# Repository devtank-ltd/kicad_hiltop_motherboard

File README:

Copyright Devtank Ltd 2021.

This documentation describes Open Hardware and is Licensed under CERN-OHL-W v2.

You may redistribute and modify this documentation under the terms of the CERN-OHL-W v2 (https://cern.ch/cern-ohl). This documentation is distributed WITHOUT ANY EXPRESS OR IMPLIED WARRANTY, INCLUDING OF MERCHANTABILITY, SATISFACTORY QUALITY AND FITNESS FOR A PARTICULAR PURPOSE. Please see the CERN-OHL-W v2 for applicable conditions

Source location: git@github.com:devtank-ltd/hiltop_motherboard.git 

As per CERN-OHL-W v2 section 4.1, should You produce hardware based on these sources, You must maintain the   Source Location visible on the external case of the HILTOP or other product you make using this documentation.

This folder contains HILTOP Motherboard hardware schematics, PCB layout and BOM files. 

You will need Kicad to open hardware design files.

HILTOP Motherboards and other test and measurement products can be purchased directly from Devtank Ltd.

Please contact:
Tim Telford
CTO - Devtank Ltd
+44 (0)1332 650944

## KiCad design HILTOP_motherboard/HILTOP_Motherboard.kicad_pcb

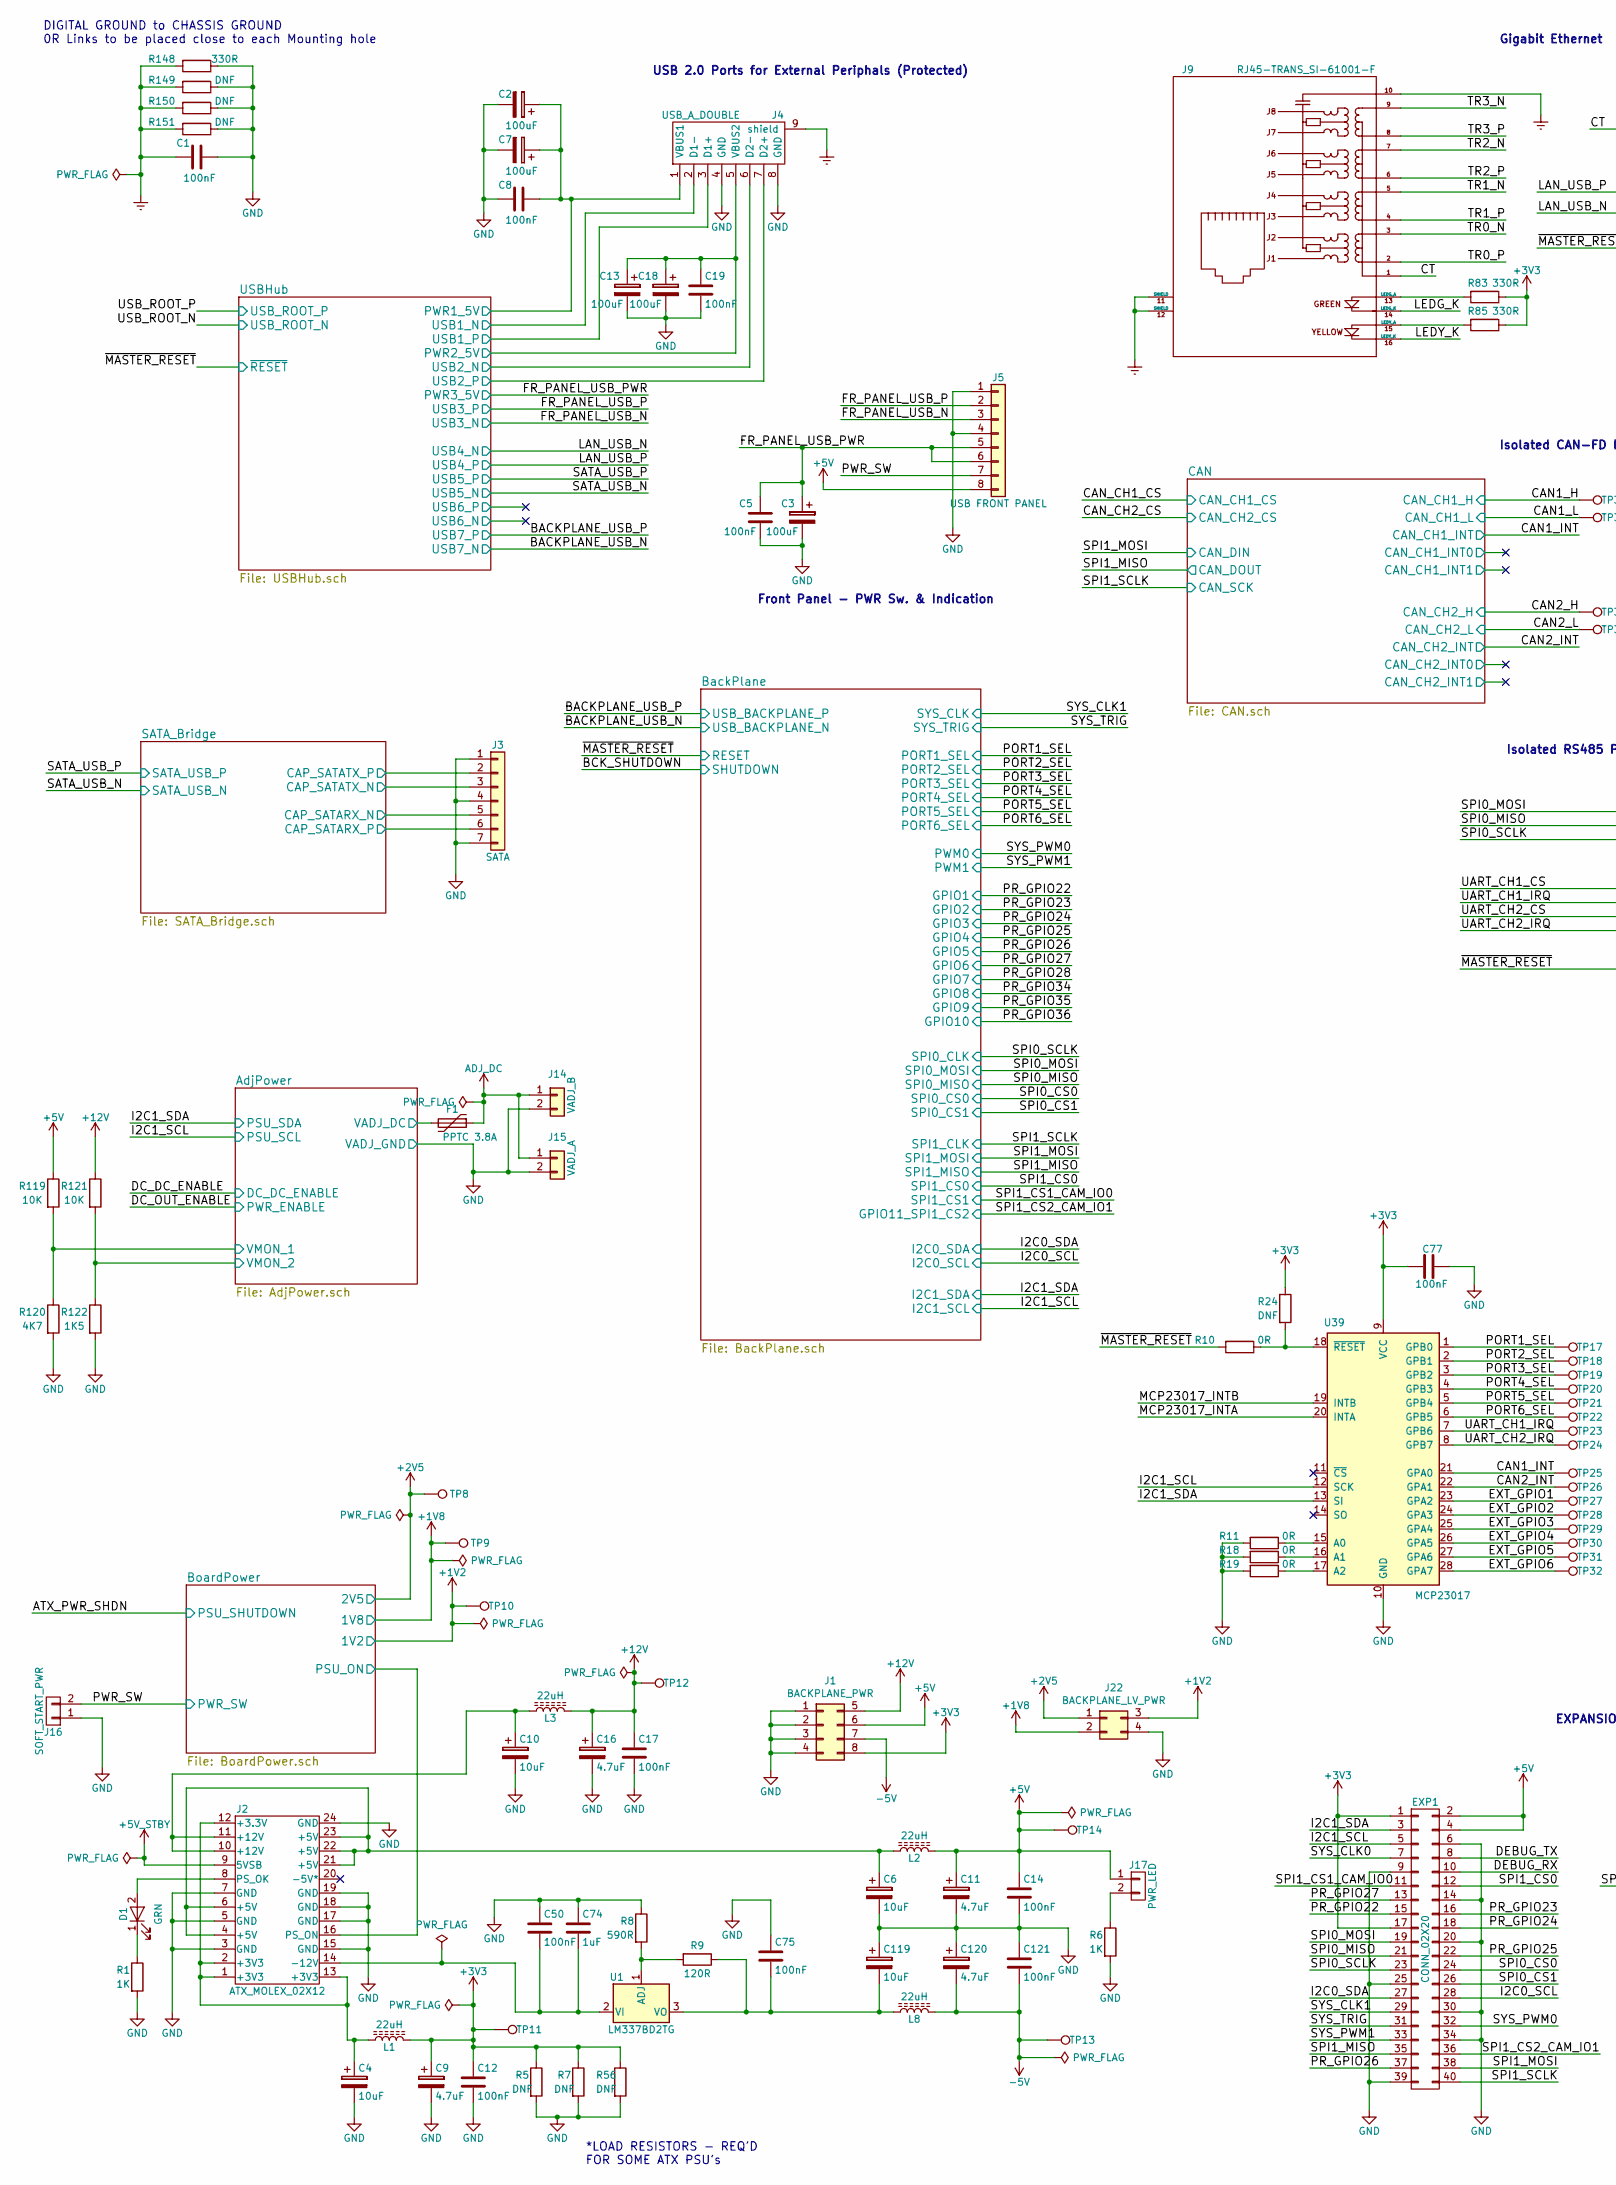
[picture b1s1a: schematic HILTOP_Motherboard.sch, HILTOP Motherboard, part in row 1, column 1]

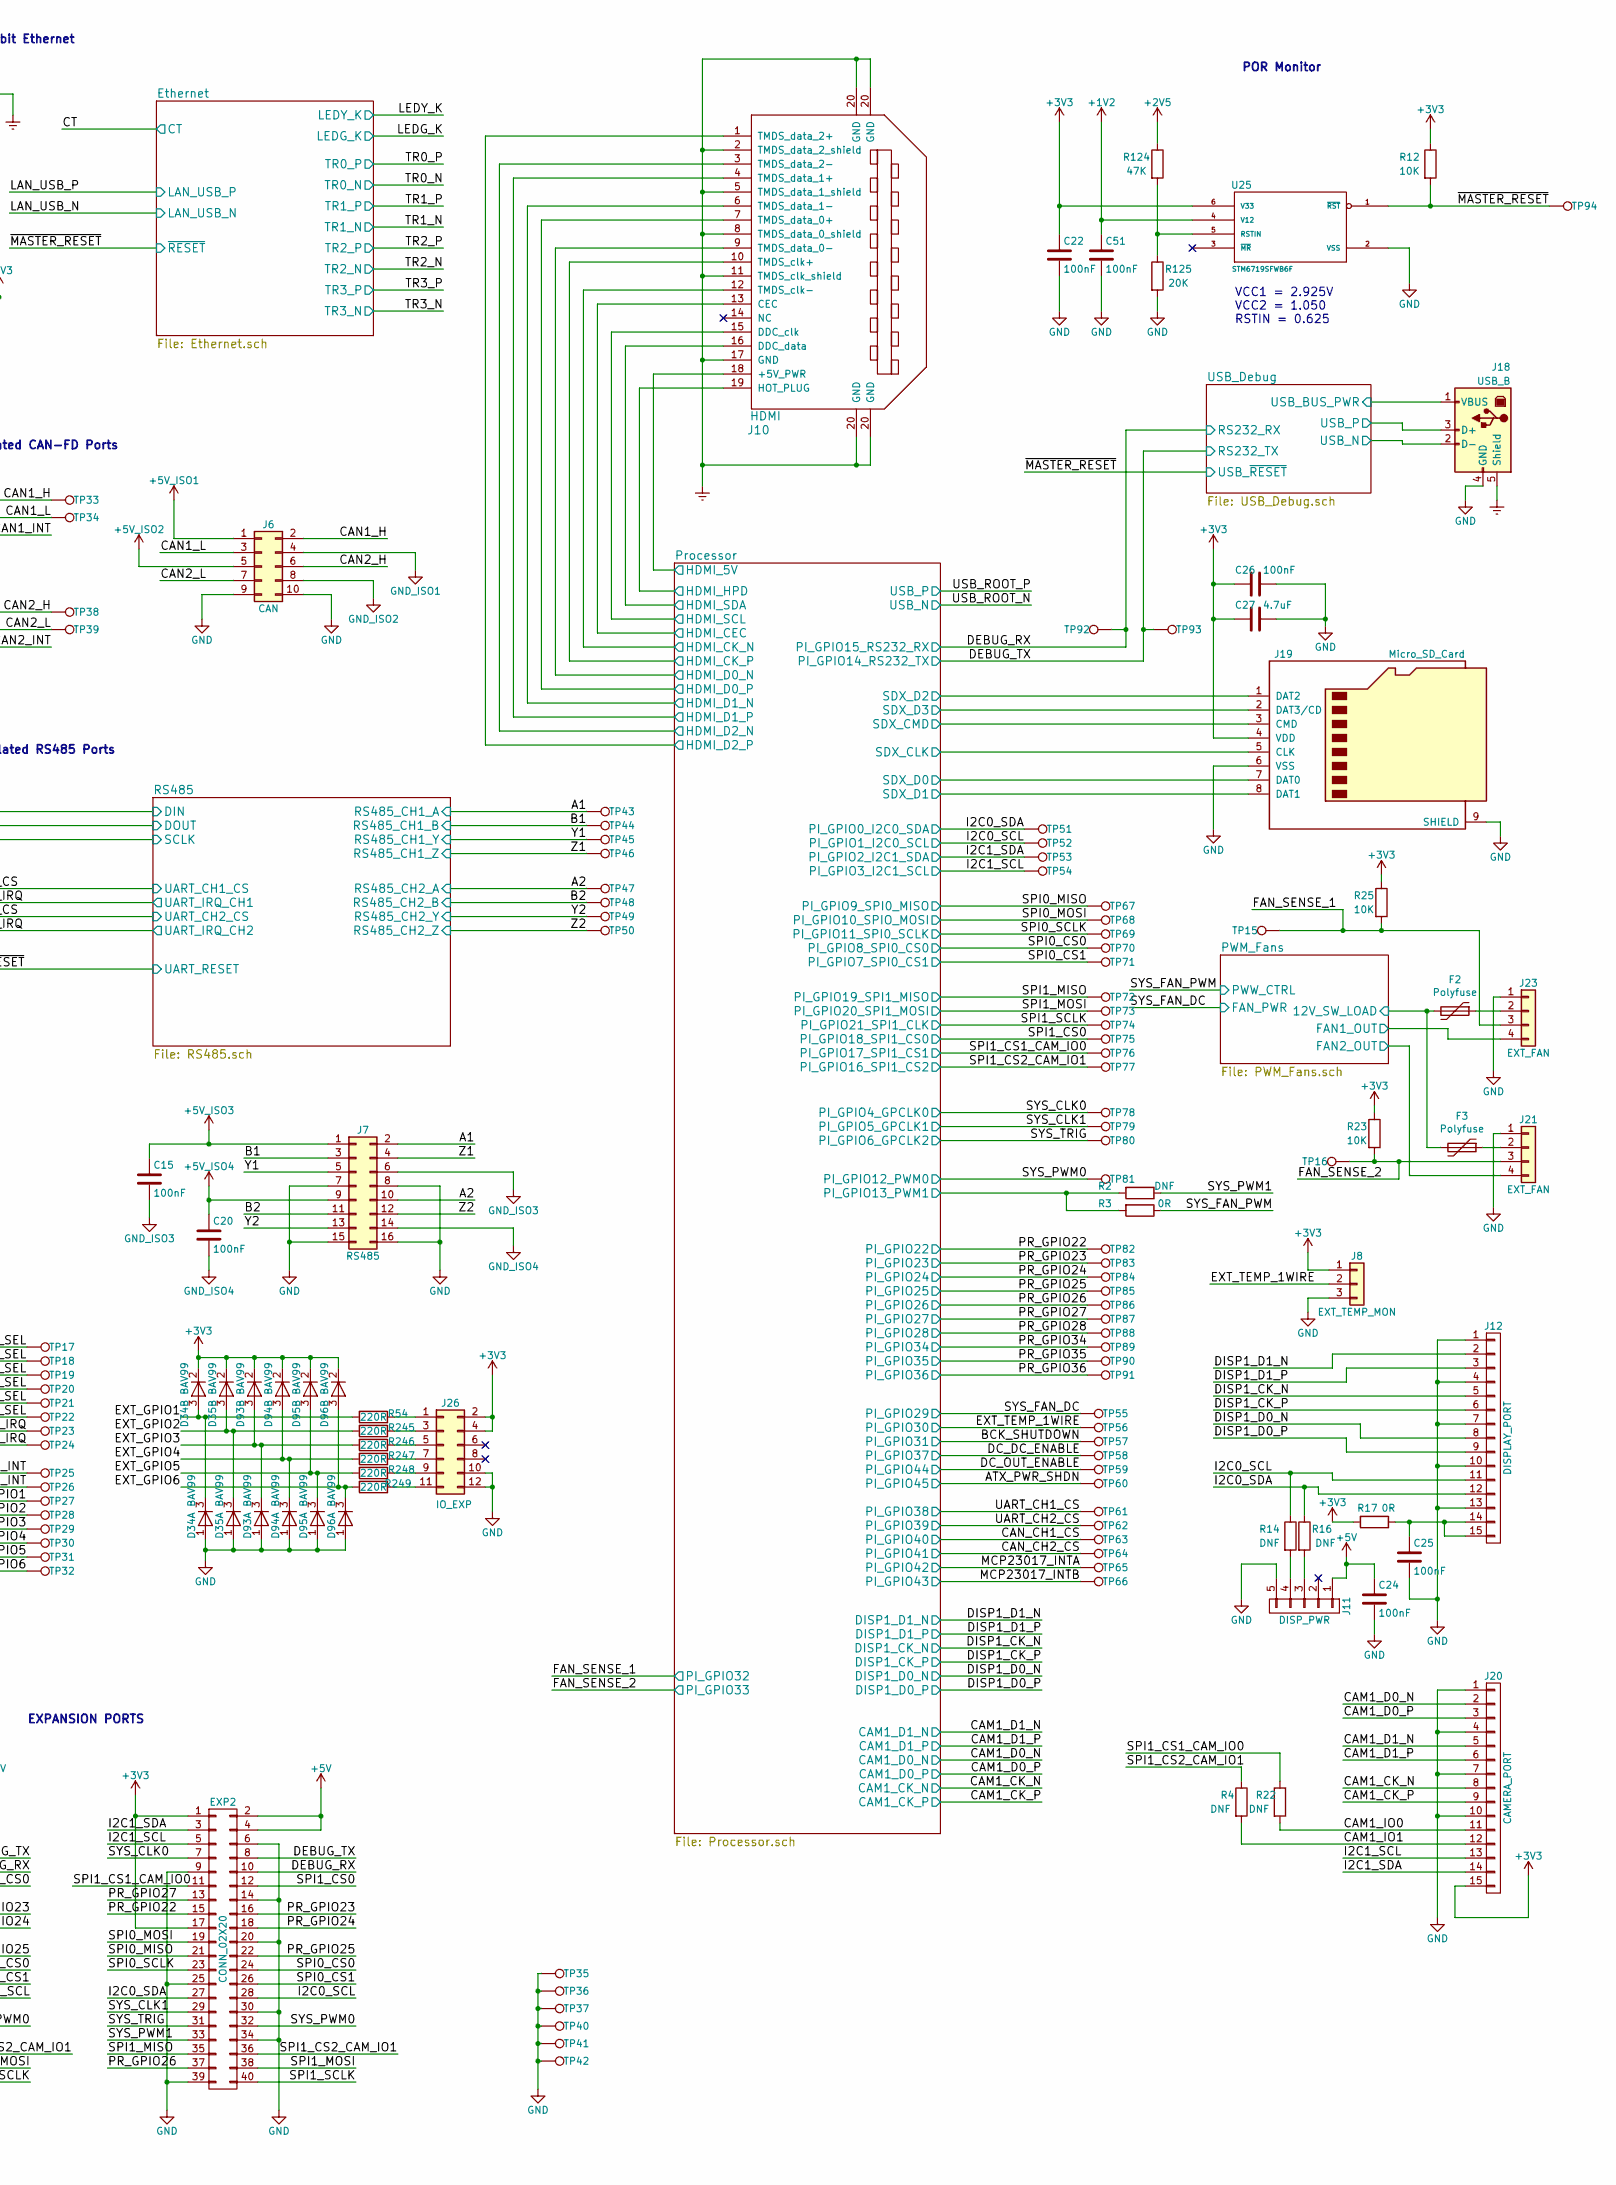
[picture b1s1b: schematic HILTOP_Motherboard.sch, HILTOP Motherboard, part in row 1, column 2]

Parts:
C1: 100nF; C_1210_3225Metric
C2, C3, C7, C13, C18: 100uF; CP_Elec_6.3x7.7
C4, C6, C10, C119: 10uF; CP_Elec_6.3x5.3
C5, C8, C12, C14, C15, C17, C19, C20, C22, C24, C25, C26, C50, C75, C77, C121: 100nF; C_0603_1608Metric
C9, C11, C16, C120: 4.7uF; CP_Elec_5x5.3
C27: 4.7uF; C_0805_2012Metric
C51: 100nF; C_0402_1005Metric
C74: 1uF; C_0805_2012Metric
D1: GRN; LED_0402_1005Metric
D34, D35, D93, D94, D95, D96: BAV99; SOT-23
EXP1, EXP2: CONN_02X20; IDC-Header_2x20_P2.54mm_Vertical
F1: PPTC 3.8A; Fuse_Bourns_MF-RHT200
F2, F3: Polyfuse; Fuse_1206_3216Metric
J1: BACKPLANE_PWR; Molex_Mini-Fit_Jr_5566-08A_2x04_P4.20mm_Vertical
J2: ATX_MOLEX_02X12; Molex_MiniFit-JR-5556-24A_2x12x4.20mm_Straight
J3: SATA; SATA-7_THT_VERT_1
J4: USB_A_DOUBLE; USB_A_Double_Lumberg_2410_03
J5: USB FRONT PANEL; Molex_Picoflex_90325-0008_2x04_P1.27mm_Vertical
J6: CAN; Molex_Picoflex_90325-0010_2x05_P1.27mm_Vertical
J7: RS485; Molex_Picoflex_90325-0016_2x08_P1.27mm_Vertical
J8: EXT_TEMP_MON; Molex_KK-254_AE-6410-03A_1x03_P2.54mm_Vertical
J9: RJ45-TRANS_SI-61001-F; RJ45_TRANSFO_STEWART
J10: HDMI; FCI_10029449-11RLF
J11: DISP_PWR; Molex_KK-254_AE-6410-05A_1x05_P2.54mm_Vertical
J12: DISPLAY_PORT; DSI_FCC15W_VERT
J14: VADJ_B; Molex_MiniFit-JR-5556-02A_2x01x4.20mm_Straight
J15: VADJ_A; Molex_MiniFit-JR-5556-02A_2x01x4.20mm_Straight
J16: SOFT_START_PWR; Pin_Header_Straight_1x02_Pitch2.54mm
J17: PWR_LED; Pin_Header_Straight_1x02_Pitch2.54mm
J18: USB_B; USB_B_Horizontal
J19: Micro_SD_Card; uSD_MSDC-PP03
J20: CAMERA_PORT; DSI_FCC15W_VERT
J21, J23: EXT_FAN; Molex_KK-254_AE-6410-04A_1x04_P2.54mm_Vertical
J22: BACKPLANE_LV_PWR; Molex_Mini-Fit_Jr_5566-04A_2x02_P4.20mm_Vertical
J26: IO_EXP; IDC-Header_2x06_P2.54mm_Vertical
L1, L2, L3, L8: 22uH; Inductor_8x8
R1, R6: 1K; R_0603_1608Metric
R2, R4, R14, R16, R22, R24: DNF; R_0603_1608Metric
R3, R10, R11, R17, R18, R19: 0R; R_0603_1608Metric
R5, R7, R56: DNF; R_1206_3216Metric
R8: 590R; R_1206_3216Metric
R9: 120R; R_0603_1608Metric
R12, R23, R25, R119, R121: 10K; R_0603_1608Metric
R54, R245, R246, R247, R248, R249: 220R; R_0402_1005Metric
R83, R85: 330R; R_0603_1608Metric
R120: 4K7; R_0603_1608Metric
R122: 1K5; R_0603_1608Metric
R124: 47K; R_0603_1608Metric
R125: 20K; R_0603_1608Metric
R148: 330R; R_1210_3225Metric
R149, R150, R151: DNF; R_1210_3225Metric
TP8, TP9, TP10, TP11, TP12, TP13, TP14, TP15, TP16, TP17, TP18, TP19, TP20, TP21, TP22, TP23, TP24, TP25, TP26, TP27, TP28, TP29, TP30, TP31, TP32, TP33, TP34, TP35, TP36, TP37, TP38, TP39, TP40, TP41, TP42, TP43, TP44, TP45, TP46, TP47, TP48, TP49, TP50, TP51, TP52, TP53, TP54, TP55, TP56, TP57, TP58, TP59, TP60, TP61, TP62, TP63, TP64, TP65, TP66, TP67, TP68, TP69, TP70, TP71, TP72, TP73, TP74, TP75, TP76, TP77, TP78, TP79, TP80, TP81, TP82, TP83, TP84, TP85, TP86, TP87, TP88, TP89, TP90, TP91, TP92, TP93, TP94: TP; TestPoint_THTPad_D1.0mm_Drill0.5mm
U1: LM337BD2TG; TO-263-2
U25: STM6719SFWB6F; TSOT-23-6
U39: MCP23017; SSOP-28_5.3x10.2mm_P0.65mm

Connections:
+1V2: C51.1, J22.3, TP10.1, U25.4 (V12); also elsewhere on the board
+1V8: J22.2, TP9.1; also elsewhere on the board
+2V5: J22.1, R124.1, TP8.1; also elsewhere on the board
+2V5_LAN_A: J9.1; also elsewhere on the board
+3V3: C9.1, C12.1, C22.1, C26.2, C27.2, C77.2, D34.2 (K), D35.2 (K), D93.2 (K), D94.2 (K), D95.2 (K), D96.2 (K), EXP1.1, EXP1.17, EXP2.1, EXP2.17, J1.8, J8.1, J19.4 (VDD), J20.15, J26.2, J26.4, L1.2, R5.1, R7.1, R12.1, R17.2, R23.1, R24.1, R25.1, R56.1, R83.1, R85.1, TP11.1, U25.6 (V33), U39.9 (VCC); also elsewhere on the board
+5V_ISO1: J6.1; also elsewhere on the board
+5V_ISO2: J6.5; also elsewhere on the board
+5V_STBY: J2.9 (5VSB); also elsewhere on the board
+12V: C16.1, C17.1, J1.5, L3.2, R121.1, TP12.1; also elsewhere on the board
-5V: C120.2, C121.2, J1.7, L8.2, TP13.1; also elsewhere on the board
/A1: J7.2, TP43.1; also elsewhere on the board
/A2: J7.10, TP47.1; also elsewhere on the board
/ATX_PWR_SHDN: TP60.1; also elsewhere on the board
/AdjPower/VADJ_DC: F1.2; also elsewhere on the board
/AdjPower/VMON_1: R119.2, R120.1; also elsewhere on the board
/AdjPower/VMON_2: R121.2, R122.1; also elsewhere on the board
/B1: J7.3, TP44.1; also elsewhere on the board
/B2: J7.11, TP48.1; also elsewhere on the board
/BCK_SHUTDOWN: TP57.1; also elsewhere on the board
/BoardPower/PSU_ON: J2.16 (PS_ON); also elsewhere on the board
/CAM1_CK_N: J20.8; also elsewhere on the board
/CAM1_CK_P: J20.9; also elsewhere on the board
/CAM1_D0_N: J20.2; also elsewhere on the board
/CAM1_D0_P: J20.3; also elsewhere on the board
/CAM1_D1_N: J20.5; also elsewhere on the board
/CAM1_D1_P: J20.6; also elsewhere on the board
/CAM1_IO0: J20.11, R22.2
/CAM1_IO1: J20.12, R4.2
/CAN1_H: J6.2, TP33.1; also elsewhere on the board
/CAN1_INT: TP25.1, U39.21 (GPA0); also elsewhere on the board
/CAN1_L: J6.3, TP34.1; also elsewhere on the board
/CAN2_H: J6.6, TP38.1; also elsewhere on the board
/CAN2_INT: TP26.1, U39.22 (GPA1); also elsewhere on the board
/CAN2_L: J6.7, TP39.1; also elsewhere on the board
/CAN_CH1_CS: TP63.1; also elsewhere on the board
/CAN_CH2_CS: TP64.1; also elsewhere on the board
/DC_DC_ENABLE: TP58.1; also elsewhere on the board
/DC_OUT_ENABLE: TP59.1; also elsewhere on the board
/DEBUG_RX: EXP1.10, EXP2.10, TP92.1; also elsewhere on the board
/DEBUG_TX: EXP1.8, EXP2.8, TP93.1; also elsewhere on the board
/DISP1_CK_N: J12.5; also elsewhere on the board
/DISP1_CK_P: J12.6; also elsewhere on the board
/DISP1_D0_N: J12.8; also elsewhere on the board
/DISP1_D0_P: J12.9; also elsewhere on the board
/DISP1_D1_N: J12.2; also elsewhere on the board
/DISP1_D1_P: J12.3; also elsewhere on the board
/EXT_GPIO1: D34.3 (K), R54.2, TP27.1, U39.23 (GPA2)
/EXT_GPIO2: D35.3 (K), R245.2, TP28.1, U39.24 (GPA3)
/EXT_GPIO3: D93.3 (K), R246.2, TP29.1, U39.25 (GPA4)
/EXT_GPIO4: D94.3 (K), R247.2, TP30.1, U39.26 (GPA5)
/EXT_GPIO5: D95.3 (K), R248.2, TP31.1, U39.27 (GPA6)
/EXT_GPIO6: D96.3 (K), R249.2, TP32.1, U39.28 (GPA7)
/EXT_TEMP_1WIRE: J8.2, TP56.1; also elsewhere on the board
/FAN_SENSE_1: J23.3, R25.2, TP15.1; also elsewhere on the board
/FAN_SENSE_2: J21.3, R23.2, TP16.1; also elsewhere on the board
/FR_PANEL_USB_N: J5.3; also elsewhere on the board
/FR_PANEL_USB_P: J5.2; also elsewhere on the board
/FR_PANEL_USB_PWR: C3.1, C5.1, J5.5, J5.6; also elsewhere on the board
/I2C0_SCL: EXP1.28, EXP2.28, J12.11, R14.1, TP52.1; also elsewhere on the board
/I2C0_SDA: EXP1.27, EXP2.27, J12.12, R16.1, TP51.1; also elsewhere on the board
/I2C1_SCL: EXP1.5, EXP2.5, J20.13, TP54.1, U39.12 (SCK); also elsewhere on the board
/I2C1_SDA: EXP1.3, EXP2.3, J20.14, TP53.1, U39.13 (SI); also elsewhere on the board
/LEDG_K: J9.14 (LEDG_K); also elsewhere on the board
/LEDY_K: J9.16 (LEDY_K); also elsewhere on the board
/MCP23017_INTA: TP65.1, U39.20 (INTA); also elsewhere on the board
/MCP23017_INTB: TP66.1, U39.19 (INTB); also elsewhere on the board
/PORT1_SEL: TP17.1, U39.1 (GPB0); also elsewhere on the board
/PORT2_SEL: TP18.1, U39.2 (GPB1); also elsewhere on the board
/PORT3_SEL: TP19.1, U39.3 (GPB2); also elsewhere on the board
/PORT4_SEL: TP20.1, U39.4 (GPB3); also elsewhere on the board
/PORT5_SEL: TP21.1, U39.5 (GPB4); also elsewhere on the board
/PORT6_SEL: TP22.1, U39.6 (GPB5); also elsewhere on the board
/PR_GPIO22: EXP1.15, EXP2.15, TP82.1; also elsewhere on the board
/PR_GPIO23: EXP1.16, EXP2.16, TP83.1; also elsewhere on the board
/PR_GPIO24: EXP1.18, EXP2.18, TP84.1; also elsewhere on the board
/PR_GPIO25: EXP1.22, EXP2.22, TP85.1; also elsewhere on the board
/PR_GPIO26: EXP1.37, EXP2.37, TP86.1; also elsewhere on the board
/PR_GPIO27: EXP1.13, EXP2.13, TP87.1; also elsewhere on the board
/PR_GPIO28: TP88.1; also elsewhere on the board
/PR_GPIO34: TP89.1; also elsewhere on the board
/PR_GPIO35: TP90.1; also elsewhere on the board
/PR_GPIO36: TP91.1; also elsewhere on the board
/PWM_Fans/12V_SW_LOAD: F2.2, F3.2; also elsewhere on the board
/PWM_Fans/FAN1_OUT: J23.4; also elsewhere on the board
/PWM_Fans/FAN2_OUT: J21.4; also elsewhere on the board
/PWR_SW: J5.7, J16.2; also elsewhere on the board
/Processor/HDMI_5V: J10.18 (+5V_PWR); also elsewhere on the board
/Processor/HDMI_CEC: J10.13 (CEC); also elsewhere on the board
/Processor/HDMI_CK_N: J10.12 (TMDS_clk-); also elsewhere on the board
/Processor/HDMI_CK_P: J10.10 (TMDS_clk+); also elsewhere on the board
/Processor/HDMI_D0_N: J10.9 (TMDS_data_0-); also elsewhere on the board
/Processor/HDMI_D0_P: J10.7 (TMDS_data_0+); also elsewhere on the board
/Processor/HDMI_D1_N: J10.6 (TMDS_data_1-); also elsewhere on the board
/Processor/HDMI_D1_P: J10.4 (TMDS_data_1+); also elsewhere on the board
/Processor/HDMI_D2_N: J10.3 (TMDS_data_2-); also elsewhere on the board
/Processor/HDMI_D2_P: J10.1 (TMDS_data_2+); also elsewhere on the board
/Processor/HDMI_HPD: J10.19 (HOT_PLUG); also elsewhere on the board
/Processor/HDMI_SCL: J10.15 (DDC_clk); also elsewhere on the board
/Processor/HDMI_SDA: J10.16 (DDC_data); also elsewhere on the board
/Processor/PI_GPIO13_PWM1: R2.2, R3.2; also elsewhere on the board
/Processor/SDX_CLK: J19.5 (CLK); also elsewhere on the board
/Processor/SDX_CMD: J19.3 (CMD); also elsewhere on the board
/Processor/SDX_D0: J19.7 (DAT0); also elsewhere on the board
/Processor/SDX_D1: J19.8 (DAT1); also elsewhere on the board
/Processor/SDX_D2: J19.1 (DAT2); also elsewhere on the board
/Processor/SDX_D3: J19.2 (DAT3/CD); also elsewhere on the board
/SATA_Bridge/CAP_SATARX_N: J3.5; also elsewhere on the board
/SATA_Bridge/CAP_SATARX_P: J3.6; also elsewhere on the board
/SATA_Bridge/CAP_SATATX_N: J3.3; also elsewhere on the board
/SATA_Bridge/CAP_SATATX_P: J3.2; also elsewhere on the board
/SPI0_CS0: EXP1.24, EXP2.24, TP70.1; also elsewhere on the board
/SPI0_CS1: EXP1.26, EXP2.26, TP71.1; also elsewhere on the board
/SPI0_MISO: EXP1.21, EXP2.21, TP67.1; also elsewhere on the board
/SPI0_MOSI: EXP1.19, EXP2.19, TP68.1; also elsewhere on the board
/SPI0_SCLK: EXP1.23, EXP2.23, TP69.1; also elsewhere on the board
/SPI1_CS0: EXP1.12, EXP2.12, TP75.1; also elsewhere on the board
/SPI1_CS1_CAM_IO0: EXP1.11, EXP2.11, R22.1, TP76.1; also elsewhere on the board
/SPI1_CS2_CAM_IO1: EXP1.36, EXP2.36, R4.1, TP77.1; also elsewhere on the board
/SPI1_MISO: EXP1.35, EXP2.35, TP72.1; also elsewhere on the board
/SPI1_MOSI: EXP1.38, EXP2.38, TP73.1; also elsewhere on the board
/SPI1_SCLK: EXP1.40, EXP2.40, TP74.1; also elsewhere on the board
/SYS_CLK0: EXP1.7, EXP2.7, TP78.1; also elsewhere on the board
/SYS_CLK1: EXP1.29, EXP2.29, TP79.1; also elsewhere on the board
/SYS_FAN_DC: TP55.1; also elsewhere on the board
/SYS_FAN_PWM: R3.1; also elsewhere on the board
/SYS_PWM0: EXP1.32, EXP2.32, TP81.1; also elsewhere on the board
/SYS_PWM1: EXP1.33, EXP2.33, R2.1; also elsewhere on the board
/SYS_TRIG: EXP1.31, EXP2.31, TP80.1; also elsewhere on the board
/TR0_N: J9.3; also elsewhere on the board
/TR0_P: J9.2; also elsewhere on the board
/TR1_N: J9.5; also elsewhere on the board
/TR1_P: J9.4; also elsewhere on the board
/TR2_N: J9.7; also elsewhere on the board
/TR2_P: J9.6; also elsewhere on the board
/TR3_N: J9.9; also elsewhere on the board
/TR3_P: J9.8; also elsewhere on the board
/UART_CH1_CS: TP61.1; also elsewhere on the board
/UART_CH1_IRQ: TP23.1, U39.7 (GPB6); also elsewhere on the board
/UART_CH2_CS: TP62.1; also elsewhere on the board
/UART_CH2_IRQ: TP24.1, U39.8 (GPB7); also elsewhere on the board
/USBHub/PWR1_5V: C2.1, C7.1, C8.1, J4.1 (VBUS1); also elsewhere on the board
/USBHub/PWR2_5V: C13.1, C18.1, C19.1, J4.5 (VBUS2); also elsewhere on the board
/USBHub/USB1_N: J4.2 (D1-); also elsewhere on the board
/USBHub/USB1_P: J4.3 (D1+); also elsewhere on the board
/USBHub/USB2_N: J4.6 (D2-); also elsewhere on the board
/USBHub/USB2_P: J4.7 (D2+); also elsewhere on the board
/USB_Debug/USB_BUS_PWR: J18.1 (VBUS); also elsewhere on the board
/USB_Debug/USB_N: J18.2 (D-); also elsewhere on the board
/USB_Debug/USB_P: J18.3 (D+); also elsewhere on the board
/Y1: J7.5, TP45.1; also elsewhere on the board
/Y2: J7.13, TP49.1; also elsewhere on the board
/Z1: J7.4, TP46.1; also elsewhere on the board
/Z2: J7.12, TP50.1; also elsewhere on the board
/~MASTER_RESET: R10.2, R12.2, TP94.1, U25.1 (~RST); also elsewhere on the board
ADJ_DC: F1.1, J14.1, J15.1
Earth: C1.2, J4.9 (shield), J9.10, J9.11 (SHIELD), J9.12 (SHIELD), J10.2 (TMDS_data_2_shield), J10.5 (TMDS_data_1_shield), J10.8 (TMDS_data_0_shield), J10.11 (TMDS_clk_shield), J10.17 (GND), J10.20 (GND), J18.5 (Shield), R148.2, R149.2, R150.2, R151.2
GND: C1.1, C2.2, C3.2, C4.2, C5.2, C6.2, C7.2, C8.2, C9.2, C10.2, C11.2, C12.2, C13.2, C14.2, C16.2, C17.2, C18.2, C19.2, C22.2, C24.2, C25.2, C26.1, C27.1, C50.1, C51.2, C74.1, C75.1, C77.1, C119.1, C120.1, C121.1, D34.1 (A), D35.1 (A), D93.1 (A), D94.1 (A), D95.1 (A), D96.1 (A), EXP1.6, EXP1.9, EXP1.14, EXP1.20, EXP1.25, EXP1.30, EXP1.34, EXP1.39, EXP2.6, EXP2.9, EXP2.14, EXP2.20, EXP2.25, EXP2.30, EXP2.34, EXP2.39, J1.1, J1.2, J1.3, J1.4, J2.3 (GND), J2.5 (GND), J2.7 (GND), J2.15 (GND), J2.17 (GND), J2.18 (GND), J2.19 (GND), J2.24 (GND), J3.1, J3.4, J3.7, J4.4 (GND), J4.8 (GND), J5.1, J5.4, J6.9, J6.10, J7.7, J7.8, J7.15, J7.16, J8.3, J11.5, J12.1, J12.4, J12.7, J12.10, J12.13, J14.2, J15.2, J16.1, J18.4 (GND), J19.6 (VSS), J19.9 (SHIELD), J20.1, J20.4, J20.7, J20.10, J21.1, J22.4, J23.1, J26.10, J26.12, R1.2, R5.2, R6.2, R7.2, R8.1, R11.2, R18.2, R19.2, R56.2, R120.2, R122.2, R125.2, R148.1, R149.1, R150.1, R151.1, TP35.1, TP36.1, TP37.1, TP40.1, TP41.1, TP42.1, U25.2 (VSS), U39.10 (GND); also elsewhere on the board
GND_ISO1: J6.4; also elsewhere on the board
GND_ISO2: J6.8; also elsewhere on the board
GND_ISO3: C15.2, J7.6; also elsewhere on the board
GND_ISO4: C20.2, J7.14; also elsewhere on the board
unnamed: C4.1, J2.1 (+3V3), J2.2 (+3V3), J2.12 (+3.3V), J2.13 (+3V3), L1.1
unnamed: C6.1, J2.4 (+5V), J2.6 (+5V), J2.21 (+5V), J2.22 (+5V), J2.23 (+5V), L2.1
unnamed: C10.1, J2.10 (+12V), J2.11 (+12V), L3.1
unnamed: C25.1, J12.14, J12.15, R17.1
unnamed: C50.2, C74.2, J2.14 (-12V), U1.2 (VI)
unnamed: C75.2, C119.2, L8.1, R9.1, U1.3 (VO)
unnamed: D1.1 (K), R1.1
unnamed: D1.2 (A), J2.8 (PS_OK)
unnamed: F2.1, J23.2
unnamed: F3.1, J21.2
unnamed: J9.13 (LEDG_A), R83.2
unnamed: J9.15 (LEDY_A), R85.2
unnamed: J11.3, R16.2
unnamed: J11.4, R14.2
unnamed: J17.2, R6.1
unnamed: J26.1, R54.1
unnamed: J26.3, R245.1
unnamed: J26.5, R246.1
unnamed: J26.7, R247.1
unnamed: J26.9, R248.1
unnamed: J26.11, R249.1
unnamed: R8.2, R9.2, U1.1 (ADJ)
unnamed: R10.1, R24.2, U39.18 (~RESET)
unnamed: R11.1, U39.15 (A0)
unnamed: R18.1, U39.16 (A1)
unnamed: R19.1, U39.17 (A2)
unnamed: R124.2, R125.1, U25.5 (RSTIN)

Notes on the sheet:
*LOAD RESISTORS - REQ'D FOR SOME ATX PSU's
EXPANSION PORTS
VCC1 = 2.925V VCC2 = 1.050 RSTIN = 0.625
DIGITAL GROUND to CHASSIS GROUND 0R Links to be placed close to each Mounting hole
Isolated RS485 Ports
Isolated CAN-FD Ports
Gigabit Ethernet
USB 2.0 Ports for External Periphals (Protected)
POR Monitor
Front Panel - PWR Sw. & Indication

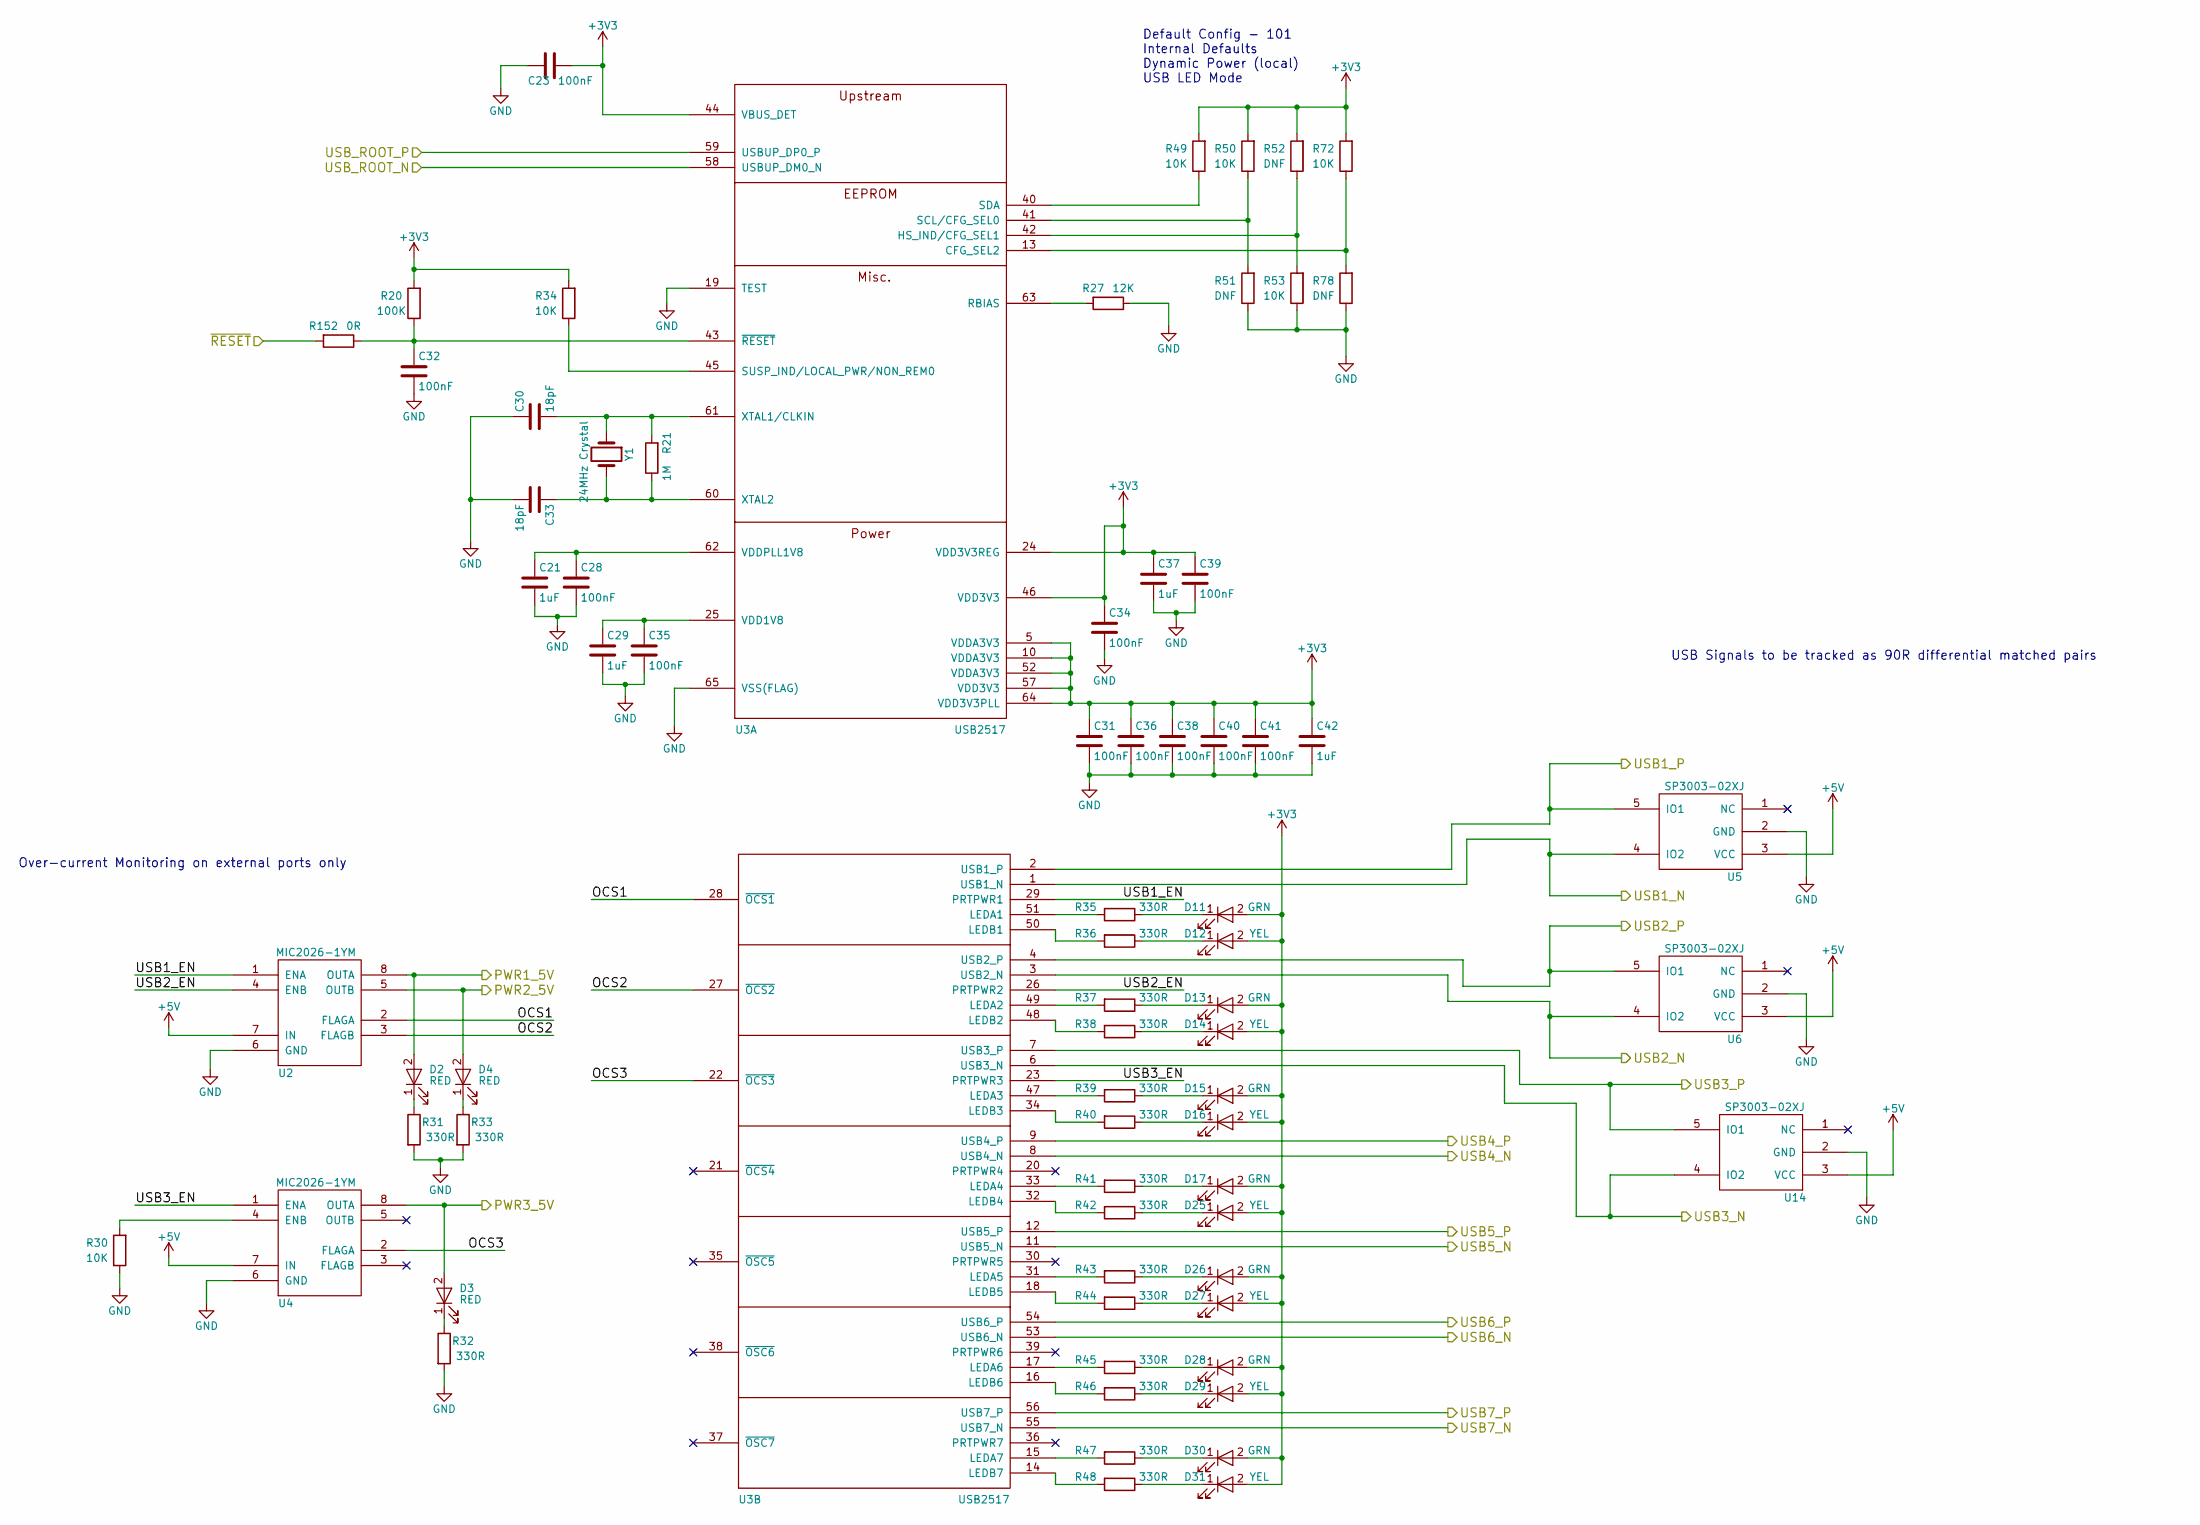
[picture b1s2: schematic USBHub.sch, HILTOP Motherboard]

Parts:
C21: 1uF; C_0603_1608Metric
C23: 100nF; C_0603_1608Metric
C28, C31, C32, C34, C35, C36, C38, C39, C40, C41: 100nF; C_0201_0603Metric
C29, C37, C42: 1uF; C_0201_0603Metric
C30, C33: 18pF; C_0201_0603Metric
D2, D3, D4: RED; LED_0402_1005Metric
D11, D13, D15, D17, D26, D28, D30: GRN; LED_0402_1005Metric
D12, D14, D16, D25, D27, D29, D31: YEL; LED_0402_1005Metric
R20: 100K; R_0603_1608Metric
R21: 1M; R_0603_1608Metric
R27: 12K; R_0603_1608Metric
R30, R34, R49, R50, R53, R72: 10K; R_0402_1005Metric
R31, R32, R33, R35, R36, R37, R38, R39, R40, R41, R42, R43, R44, R45, R46, R47, R48: 330R; R_0402_1005Metric
R51, R52, R78: DNF; R_0402_1005Metric
R152: 0R; R_0603_1608Metric
U2, U4: MIC2026-1YM; SOIC-8_3.9x4.9mm_P1.27mm
U3: USB2517; QFN-64-1EP_9x9mm_P0.5mm_EP4.7x4.7mm
U5, U6, U14: SP3003-02XJ; SC70-5
Y1: 24MHz Crystal; Crystal_SMD_7050-2Pin_7.0x5.0mm

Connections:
+3V3: C23.1, C31.1, C34.1, C36.1, C37.1, C38.1, C39.1, C40.1, C41.1, C42.1, D11.2 (A), D12.2 (A), D13.2 (A), D14.2 (A), D15.2 (A), D16.2 (A), D17.2 (A), D25.2 (A), D26.2 (A), D27.2 (A), D28.2 (A), D29.2 (A), D30.2 (A), D31.2 (A), R20.2, R34.2, R49.2, R50.2, R52.2, R72.2, U3.5 (VDDA3V3), U3.10 (VDDA3V3), U3.24 (VDD3V3REG), U3.44 (VBUS_DET), U3.46 (VDD3V3), U3.52 (VDDA3V3), U3.57 (VDD3V3), U3.64 (VDD3V3PLL); also elsewhere on the board
/BACKPLANE_USB_N: U3.55 (USB7_N); also elsewhere on the board
/BACKPLANE_USB_P: U3.56 (USB7_P); also elsewhere on the board
/FR_PANEL_USB_N: U3.6 (USB3_N), U14.4 (IO2); also elsewhere on the board
/FR_PANEL_USB_P: U3.7 (USB3_P), U14.5 (IO1); also elsewhere on the board
/FR_PANEL_USB_PWR: D3.2 (A), U4.8 (OUTA); also elsewhere on the board
/LAN_USB_N: U3.8 (USB4_N); also elsewhere on the board
/LAN_USB_P: U3.9 (USB4_P); also elsewhere on the board
/SATA_USB_N: U3.11 (USB5_N); also elsewhere on the board
/SATA_USB_P: U3.12 (USB5_P); also elsewhere on the board
/USBHub/OCS1: U2.2 (FLAGA), U3.28 (~OCS1)
/USBHub/OCS2: U2.3 (FLAGB), U3.27 (~OCS2)
/USBHub/OCS3: U3.22 (~OCS3), U4.2 (FLAGA)
/USBHub/PWR1_5V: D2.2 (A), U2.8 (OUTA); also elsewhere on the board
/USBHub/PWR2_5V: D4.2 (A), U2.5 (OUTB); also elsewhere on the board
/USBHub/USB1_EN: U2.1 (ENA), U3.29 (PRTPWR1)
/USBHub/USB1_N: U3.1 (USB1_N), U5.4 (IO2); also elsewhere on the board
/USBHub/USB1_P: U3.2 (USB1_P), U5.5 (IO1); also elsewhere on the board
/USBHub/USB2_EN: U2.4 (ENB), U3.26 (PRTPWR2)
/USBHub/USB2_N: U3.3 (USB2_N), U6.4 (IO2); also elsewhere on the board
/USBHub/USB2_P: U3.4 (USB2_P), U6.5 (IO1); also elsewhere on the board
/USBHub/USB3_EN: U3.23 (PRTPWR3), U4.1 (ENA)
/USB_ROOT_N: U3.58 (USBUP_DM0_N); also elsewhere on the board
/USB_ROOT_P: U3.59 (USBUP_DP0_P); also elsewhere on the board
/~MASTER_RESET: R152.2; also elsewhere on the board
GND: C21.2, C23.2, C28.2, C29.2, C30.1, C31.2, C32.2, C33.2, C34.2, C35.2, C36.2, C37.2, C38.2, C39.2, C40.2, C41.2, C42.2, R27.1, R30.1, R31.2, R32.2, R33.2, R51.1, R53.1, R78.1, U2.6 (GND), U3.19 (TEST), U3.65 (VSS(FLAG)), U4.6 (GND), U5.2 (GND), U6.2 (GND), U14.2 (GND); also elsewhere on the board
unnamed: C21.1, C28.1, U3.62 (VDDPLL1V8)
unnamed: C29.1, C35.1, U3.25 (VDD1V8)
unnamed: C30.2, R21.2, U3.61 (XTAL1/CLKIN), Y1.1
unnamed: C32.1, R20.1, R152.1, U3.43 (~RESET)
unnamed: C33.1, R21.1, U3.60 (XTAL2), Y1.2
unnamed: D2.1 (K), R31.1
unnamed: D3.1 (K), R32.1
unnamed: D4.1 (K), R33.1
unnamed: D11.1 (K), R35.1
unnamed: D12.1 (K), R36.1
unnamed: D13.1 (K), R37.1
unnamed: D14.1 (K), R38.1
unnamed: D15.1 (K), R39.1
unnamed: D16.1 (K), R40.1
unnamed: D17.1 (K), R41.1
unnamed: D25.1 (K), R42.1
unnamed: D26.1 (K), R43.1
unnamed: D27.1 (K), R44.1
unnamed: D28.1 (K), R45.1
unnamed: D29.1 (K), R46.1
unnamed: D30.1 (K), R47.1
unnamed: D31.1 (K), R48.1
unnamed: R27.2, U3.63 (RBIAS)
unnamed: R30.2, U4.4 (ENB)
unnamed: R34.1, U3.45 (SUSP_IND/LOCAL_PWR/NON_REM0)
unnamed: R35.2, U3.51 (LEDA1)
unnamed: R36.2, U3.50 (LEDB1)
unnamed: R37.2, U3.49 (LEDA2)
unnamed: R38.2, U3.48 (LEDB2)
unnamed: R39.2, U3.47 (LEDA3)
unnamed: R40.2, U3.34 (LEDB3)
unnamed: R41.2, U3.33 (LEDA4)
unnamed: R42.2, U3.32 (LEDB4)
unnamed: R43.2, U3.31 (LEDA5)
unnamed: R44.2, U3.18 (LEDB5)
unnamed: R45.2, U3.17 (LEDA6)
unnamed: R46.2, U3.16 (LEDB6)
unnamed: R47.2, U3.15 (LEDA7)
unnamed: R48.2, U3.14 (LEDB7)
unnamed: R49.1, U3.40 (SDA)
unnamed: R50.1, R51.2, U3.41 (SCL/CFG_SEL0)
unnamed: R52.1, R53.2, U3.42 (HS_IND/CFG_SEL1)
unnamed: R72.1, R78.2, U3.13 (CFG_SEL2)

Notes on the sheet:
Default Config - 101 Internal Defaults Dynamic Power (local) USB LED Mode
Over-current Monitoring on external ports only
USB Signals to be tracked as 90R differential matched pairs
